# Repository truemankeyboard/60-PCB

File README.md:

# 60% PCB
Basic 60% PCB for reference

---

## Footprint Libraries Used

- https://github.com/ai03-2725/MX_Alps_Hybrid
- https://github.com/ai03-2725/random-keyboard-parts.pretty
- https://github.com/ai03-2725/Type-C.pretty

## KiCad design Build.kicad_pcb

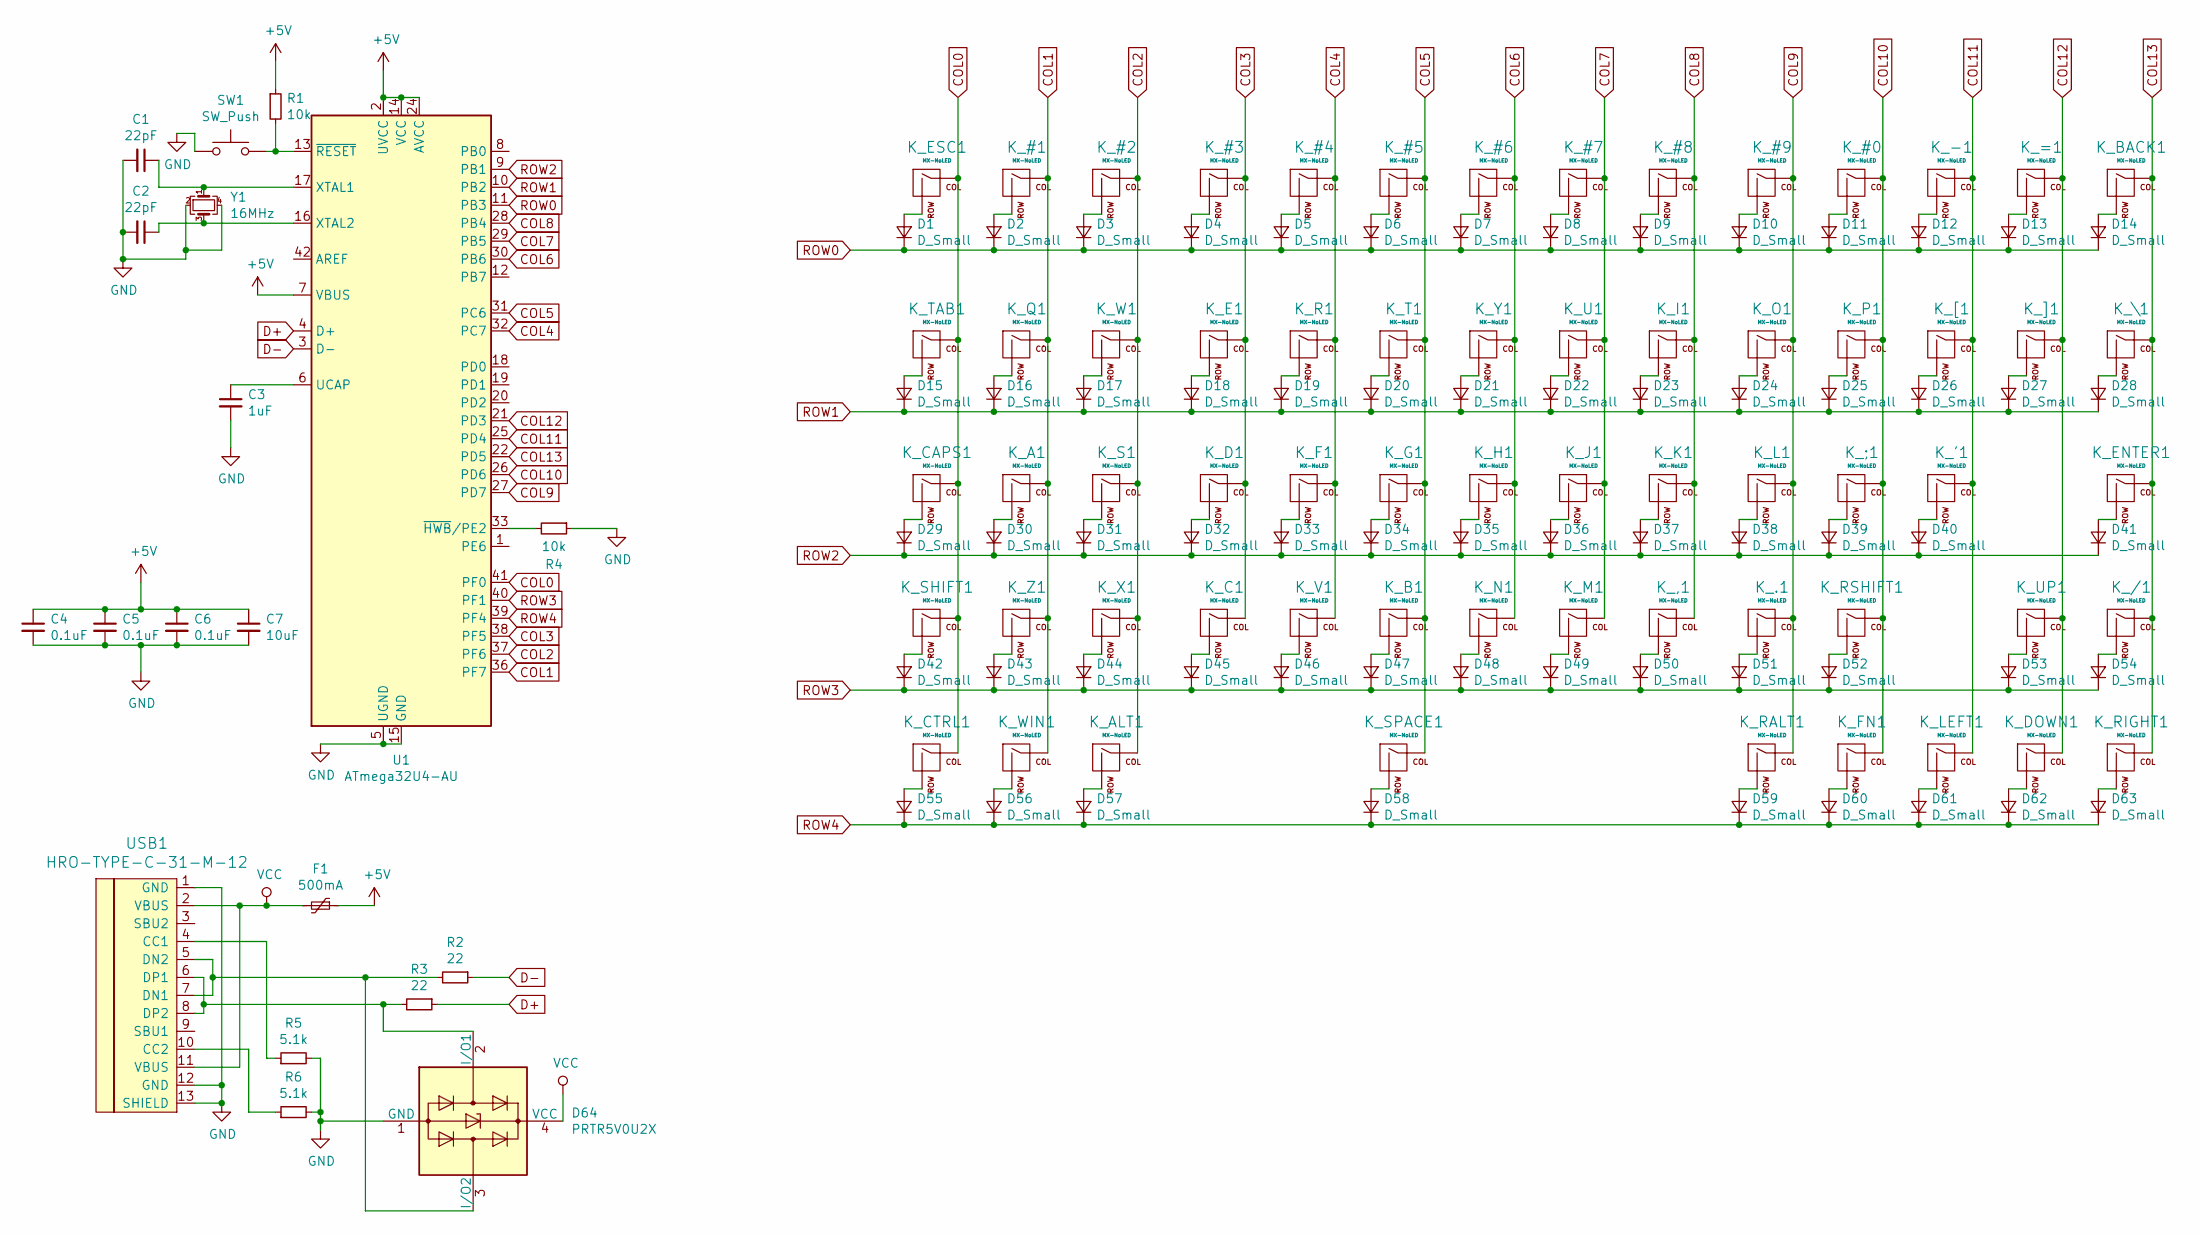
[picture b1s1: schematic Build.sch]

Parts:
C1, C2: 22pF; C_0805_2012Metric_Pad1.15x1.40mm_HandSolder
C3: 1uF; C_0805_2012Metric_Pad1.15x1.40mm_HandSolder
C4, C5, C6: 0.1uF; C_0805_2012Metric_Pad1.15x1.40mm_HandSolder
C7: 10uF; C_0805_2012Metric_Pad1.15x1.40mm_HandSolder
D1, D2, D3, D4, D5, D6, D7, D8, D9, D10, D11, D12, D13, D14, D15, D16, D17, D18, D19, D20, D21, D22, D23, D24, D25, D26, D27, D28, D29, D30, D31, D32, D33, D34, D35, D36, D37, D38, D39, D40, D41, D42, D43, D44, D45, D46, D47, D48, D49, D50, D51, D52, D53, D54, D55, D56, D57, D58, D59, D60, D61, D62, D63: D_Small; D_SOD-123
D64: PRTR5V0U2X; SOT-143
F1: 500mA; Fuse_1206_3216Metric_Pad1.42x1.75mm_HandSolder
K_#0, K_#1, K_#2, K_#3, K_#4, K_#5, K_#6, K_#7, K_#8, K_#9: MX-NoLED; MXOnly-1U-NoLED
K_'1: MX-NoLED; MXOnly-1U-NoLED
K_,1: MX-NoLED; MXOnly-1U-NoLED
K_-1: MX-NoLED; MXOnly-1U-NoLED
K_.1: MX-NoLED; MXOnly-1U-NoLED
K_/1: MX-NoLED; MXOnly-1U-NoLED
K_;1: MX-NoLED; MXOnly-1U-NoLED
K_=1: MX-NoLED; MXOnly-1U-NoLED
K_A1: MX-NoLED; MXOnly-1U-NoLED
K_ALT1: MX-NoLED; MXOnly-1.25U-NoLED
K_B1: MX-NoLED; MXOnly-1U-NoLED
K_BACK1: MX-NoLED; MXOnly-2U-NoLED
K_C1: MX-NoLED; MXOnly-1U-NoLED
K_CAPS1: MX-NoLED; MXOnly-1.75U-NoLED
K_CTRL1: MX-NoLED; MXOnly-1.25U-NoLED
K_D1: MX-NoLED; MXOnly-1U-NoLED
K_DOWN1: MX-NoLED; MXOnly-1U-NoLED
K_E1: MX-NoLED; MXOnly-1U-NoLED
K_ENTER1: MX-NoLED; MXOnly-2.25U-NoLED
K_ESC1: MX-NoLED; MXOnly-1U-NoLED
K_F1: MX-NoLED; MXOnly-1U-NoLED
K_FN1: MX-NoLED; MXOnly-1U-NoLED
K_G1: MX-NoLED; MXOnly-1U-NoLED
K_H1: MX-NoLED; MXOnly-1U-NoLED
K_I1: MX-NoLED; MXOnly-1U-NoLED
K_J1: MX-NoLED; MXOnly-1U-NoLED
K_K1: MX-NoLED; MXOnly-1U-NoLED
K_L1: MX-NoLED; MXOnly-1U-NoLED
K_LEFT1: MX-NoLED; MXOnly-1U-NoLED
K_M1: MX-NoLED; MXOnly-1U-NoLED
K_N1: MX-NoLED; MXOnly-1U-NoLED
K_O1: MX-NoLED; MXOnly-1U-NoLED
K_P1: MX-NoLED; MXOnly-1U-NoLED
K_Q1: MX-NoLED; MXOnly-1U-NoLED
K_R1: MX-NoLED; MXOnly-1U-NoLED
K_RALT1: MX-NoLED; MXOnly-1U-NoLED
K_RIGHT1: MX-NoLED; MXOnly-1U-NoLED
K_RSHIFT1: MX-NoLED; MXOnly-1.75U-NoLED
K_S1: MX-NoLED; MXOnly-1U-NoLED
K_SHIFT1: MX-NoLED; MXOnly-2.25U-NoLED
K_SPACE1: MX-NoLED; MXOnly-6.25U-NoLED
K_T1: MX-NoLED; MXOnly-1U-NoLED
K_TAB1: MX-NoLED; MXOnly-1.5U-NoLED
K_U1: MX-NoLED; MXOnly-1U-NoLED
K_UP1: MX-NoLED; MXOnly-1U-NoLED
K_V1: MX-NoLED; MXOnly-1U-NoLED
K_W1: MX-NoLED; MXOnly-1U-NoLED
K_WIN1: MX-NoLED; MXOnly-1.25U-NoLED
K_X1: MX-NoLED; MXOnly-1U-NoLED
K_Y1: MX-NoLED; MXOnly-1U-NoLED
K_Z1: MX-NoLED; MXOnly-1U-NoLED
K_[1: MX-NoLED; MXOnly-1U-NoLED
K_\1: MX-NoLED; MXOnly-1.5U-NoLED
K_]1: MX-NoLED; MXOnly-1U-NoLED
R1, R4: 10k; R_0805_2012Metric_Pad1.15x1.40mm_HandSolder
R2, R3: 22; R_0805_2012Metric_Pad1.15x1.40mm_HandSolder
R5, R6: 5.1k; R_0805_2012Metric_Pad1.15x1.40mm_HandSolder
SW1: SW_Push; SKQG-1155865
U1: ATmega32U4-AU; TQFP-44_10x10mm_P0.8mm
USB1: HRO-TYPE-C-31-M-12; HRO-TYPE-C-31-M-12-HandSoldering
Y1: 16MHz; Crystal_SMD_3225-4Pin_3.2x2.5mm_HandSoldering

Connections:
+5V: C4.1, C5.1, C6.1, C7.1, F1.1, R1.1, U1.2 (UVCC), U1.7 (VBUS), U1.14 (VCC), U1.24 (AVCC), U1.34 (VCC), U1.44 (AVCC)
COL0: K_CAPS1.1 (COL), K_CTRL1.1 (COL), K_ESC1.1 (COL), K_SHIFT1.1 (COL), K_TAB1.1 (COL), U1.41 (PF0)
COL1: K_#1.1 (COL), K_A1.1 (COL), K_Q1.1 (COL), K_WIN1.1 (COL), K_Z1.1 (COL), U1.36 (PF7)
COL2: K_#2.1 (COL), K_ALT1.1 (COL), K_S1.1 (COL), K_W1.1 (COL), K_X1.1 (COL), U1.37 (PF6)
COL3: K_#3.1 (COL), K_C1.1 (COL), K_D1.1 (COL), K_E1.1 (COL), U1.38 (PF5)
COL4: K_#4.1 (COL), K_F1.1 (COL), K_R1.1 (COL), K_V1.1 (COL), U1.32 (PC7)
COL5: K_#5.1 (COL), K_B1.1 (COL), K_G1.1 (COL), K_SPACE1.1 (COL), K_T1.1 (COL), U1.31 (PC6)
COL6: K_#6.1 (COL), K_H1.1 (COL), K_N1.1 (COL), K_Y1.1 (COL), U1.30 (PB6)
COL7: K_#7.1 (COL), K_J1.1 (COL), K_M1.1 (COL), K_U1.1 (COL), U1.29 (PB5)
COL8: K_#8.1 (COL), K_,1.1 (COL), K_I1.1 (COL), K_K1.1 (COL), U1.28 (PB4)
COL9: K_#9.1 (COL), K_.1.1 (COL), K_L1.1 (COL), K_O1.1 (COL), K_RALT1.1 (COL), U1.27 (PD7)
COL10: K_#0.1 (COL), K_;1.1 (COL), K_FN1.1 (COL), K_P1.1 (COL), K_RSHIFT1.1 (COL), U1.26 (PD6)
COL11: K_'1.1 (COL), K_-1.1 (COL), K_LEFT1.1 (COL), K_[1.1 (COL), U1.25 (PD4)
COL12: K_=1.1 (COL), K_DOWN1.1 (COL), K_UP1.1 (COL), K_]1.1 (COL), U1.21 (PD3)
COL13: K_/1.1 (COL), K_BACK1.1 (COL), K_ENTER1.1 (COL), K_RIGHT1.1 (COL), K_\1.1 (COL), U1.22 (PD5)
D+: R3.1, U1.4 (D+)
D-: R2.1, U1.3 (D-)
GND: C1.2, C2.2, C3.2, C4.2, C5.2, C6.2, C7.2, D64.1 (GND), R4.1, R5.2, R6.2, SW1.1, U1.5 (UGND), U1.15 (GND), U1.23 (GND), U1.35 (GND), U1.43 (GND), USB1.1 (GND), USB1.12 (GND), USB1.13 (SHIELD), Y1.2, Y1.4
unnamed: C1.1, U1.17 (XTAL1), Y1.1
unnamed: C2.1, U1.16 (XTAL2), Y1.3
unnamed: C3.1, U1.6 (UCAP)
unnamed: D1.2 (A), K_ESC1.2 (ROW)
unnamed: D2.2 (A), K_#1.2 (ROW)
unnamed: D3.2 (A), K_#2.2 (ROW)
unnamed: D4.2 (A), K_#3.2 (ROW)
unnamed: D5.2 (A), K_#4.2 (ROW)
unnamed: D6.2 (A), K_#5.2 (ROW)
unnamed: D7.2 (A), K_#6.2 (ROW)
unnamed: D8.2 (A), K_#7.2 (ROW)
unnamed: D9.2 (A), K_#8.2 (ROW)
unnamed: D10.2 (A), K_#9.2 (ROW)
unnamed: D11.2 (A), K_#0.2 (ROW)
unnamed: D12.2 (A), K_-1.2 (ROW)
unnamed: D13.2 (A), K_=1.2 (ROW)
unnamed: D14.2 (A), K_BACK1.2 (ROW)
unnamed: D15.2 (A), K_TAB1.2 (ROW)
unnamed: D16.2 (A), K_Q1.2 (ROW)
unnamed: D17.2 (A), K_W1.2 (ROW)
unnamed: D18.2 (A), K_E1.2 (ROW)
unnamed: D19.2 (A), K_R1.2 (ROW)
unnamed: D20.2 (A), K_T1.2 (ROW)
unnamed: D21.2 (A), K_Y1.2 (ROW)
unnamed: D22.2 (A), K_U1.2 (ROW)
unnamed: D23.2 (A), K_I1.2 (ROW)
unnamed: D24.2 (A), K_O1.2 (ROW)
unnamed: D25.2 (A), K_P1.2 (ROW)
unnamed: D26.2 (A), K_[1.2 (ROW)
unnamed: D27.2 (A), K_]1.2 (ROW)
unnamed: D28.2 (A), K_\1.2 (ROW)
unnamed: D29.2 (A), K_CAPS1.2 (ROW)
unnamed: D30.2 (A), K_A1.2 (ROW)
unnamed: D31.2 (A), K_S1.2 (ROW)
unnamed: D32.2 (A), K_D1.2 (ROW)
unnamed: D33.2 (A), K_F1.2 (ROW)
unnamed: D34.2 (A), K_G1.2 (ROW)
unnamed: D35.2 (A), K_H1.2 (ROW)
unnamed: D36.2 (A), K_J1.2 (ROW)
unnamed: D37.2 (A), K_K1.2 (ROW)
unnamed: D38.2 (A), K_L1.2 (ROW)
unnamed: D39.2 (A), K_;1.2 (ROW)
unnamed: D40.2 (A), K_'1.2 (ROW)
unnamed: D41.2 (A), K_ENTER1.2 (ROW)
unnamed: D42.2 (A), K_SHIFT1.2 (ROW)
unnamed: D43.2 (A), K_Z1.2 (ROW)
unnamed: D44.2 (A), K_X1.2 (ROW)
unnamed: D45.2 (A), K_C1.2 (ROW)
unnamed: D46.2 (A), K_V1.2 (ROW)
unnamed: D47.2 (A), K_B1.2 (ROW)
unnamed: D48.2 (A), K_N1.2 (ROW)
unnamed: D49.2 (A), K_M1.2 (ROW)
unnamed: D50.2 (A), K_,1.2 (ROW)
unnamed: D51.2 (A), K_.1.2 (ROW)
unnamed: D52.2 (A), K_RSHIFT1.2 (ROW)
unnamed: D53.2 (A), K_UP1.2 (ROW)
unnamed: D54.2 (A), K_/1.2 (ROW)
unnamed: D55.2 (A), K_CTRL1.2 (ROW)
unnamed: D56.2 (A), K_WIN1.2 (ROW)
unnamed: D57.2 (A), K_ALT1.2 (ROW)
unnamed: D58.2 (A), K_SPACE1.2 (ROW)
unnamed: D59.2 (A), K_RALT1.2 (ROW)
unnamed: D60.2 (A), K_FN1.2 (ROW)
unnamed: D61.2 (A), K_LEFT1.2 (ROW)
unnamed: D62.2 (A), K_DOWN1.2 (ROW)
unnamed: D63.2 (A), K_RIGHT1.2 (ROW)
unnamed: D64.2 (I/O1), R3.2, USB1.6 (DP1), USB1.8 (DP2)
unnamed: D64.3 (I/O2), R2.2, USB1.5 (DN2), USB1.7 (DN1)
unnamed: R1.2, SW1.2, U1.13 (~RESET)
unnamed: R4.2, U1.33 (~HWB~/PE2)
unnamed: R5.1, USB1.4 (CC1)
unnamed: R6.1, USB1.10 (CC2)
ROW0: D1.1 (K), D2.1 (K), D3.1 (K), D4.1 (K), D5.1 (K), D6.1 (K), D7.1 (K), D8.1 (K), D9.1 (K), D10.1 (K), D11.1 (K), D12.1 (K), D13.1 (K), D14.1 (K), U1.11 (PB3)
ROW1: D15.1 (K), D16.1 (K), D17.1 (K), D18.1 (K), D19.1 (K), D20.1 (K), D21.1 (K), D22.1 (K), D23.1 (K), D24.1 (K), D25.1 (K), D26.1 (K), D27.1 (K), D28.1 (K), U1.10 (PB2)
ROW2: D29.1 (K), D30.1 (K), D31.1 (K), D32.1 (K), D33.1 (K), D34.1 (K), D35.1 (K), D36.1 (K), D37.1 (K), D38.1 (K), D39.1 (K), D40.1 (K), D41.1 (K), U1.9 (PB1)
ROW3: D42.1 (K), D43.1 (K), D44.1 (K), D45.1 (K), D46.1 (K), D47.1 (K), D48.1 (K), D49.1 (K), D50.1 (K), D51.1 (K), D52.1 (K), D53.1 (K), D54.1 (K), U1.40 (PF1)
ROW4: D55.1 (K), D56.1 (K), D57.1 (K), D58.1 (K), D59.1 (K), D60.1 (K), D61.1 (K), D62.1 (K), D63.1 (K), U1.39 (PF4)
VCC: D64.4 (VCC), F1.2, USB1.2 (VBUS), USB1.11 (VBUS)

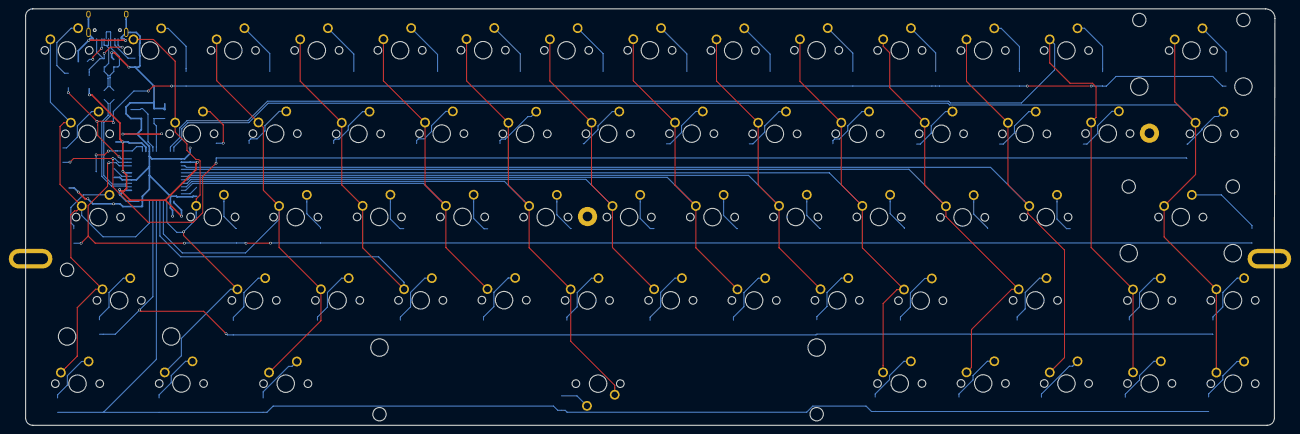
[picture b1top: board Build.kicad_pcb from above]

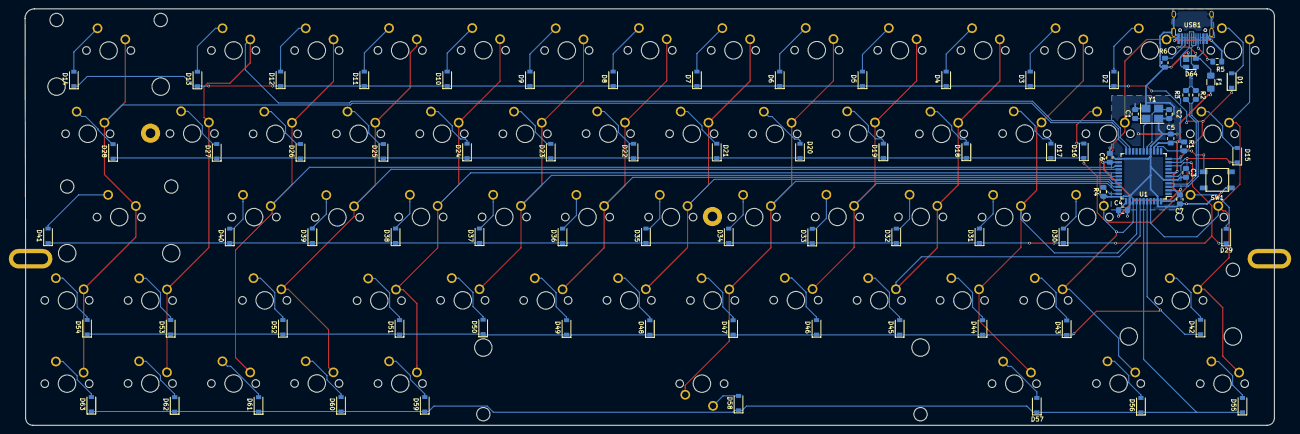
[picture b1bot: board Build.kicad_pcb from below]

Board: 2 copper layers, 285.8 x 95.2 mm, 145 parts (82 on the bottom side), 96 nets.

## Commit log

2021-06-13 PCB Files
2021-06-14 changed mounting side mounting holes
2021-06-14 Revert "changed mounting side mounting holes"
    This reverts commit 6acce158d2db27eab7de2772cbacfb22acc69852.
2021-06-14 changed side mounting holes
2021-06-14 Update fp-lib-table
2021-06-14 raw gerbers for production
    .zip these files or download the pre zipped one from the releases to get a format for production
